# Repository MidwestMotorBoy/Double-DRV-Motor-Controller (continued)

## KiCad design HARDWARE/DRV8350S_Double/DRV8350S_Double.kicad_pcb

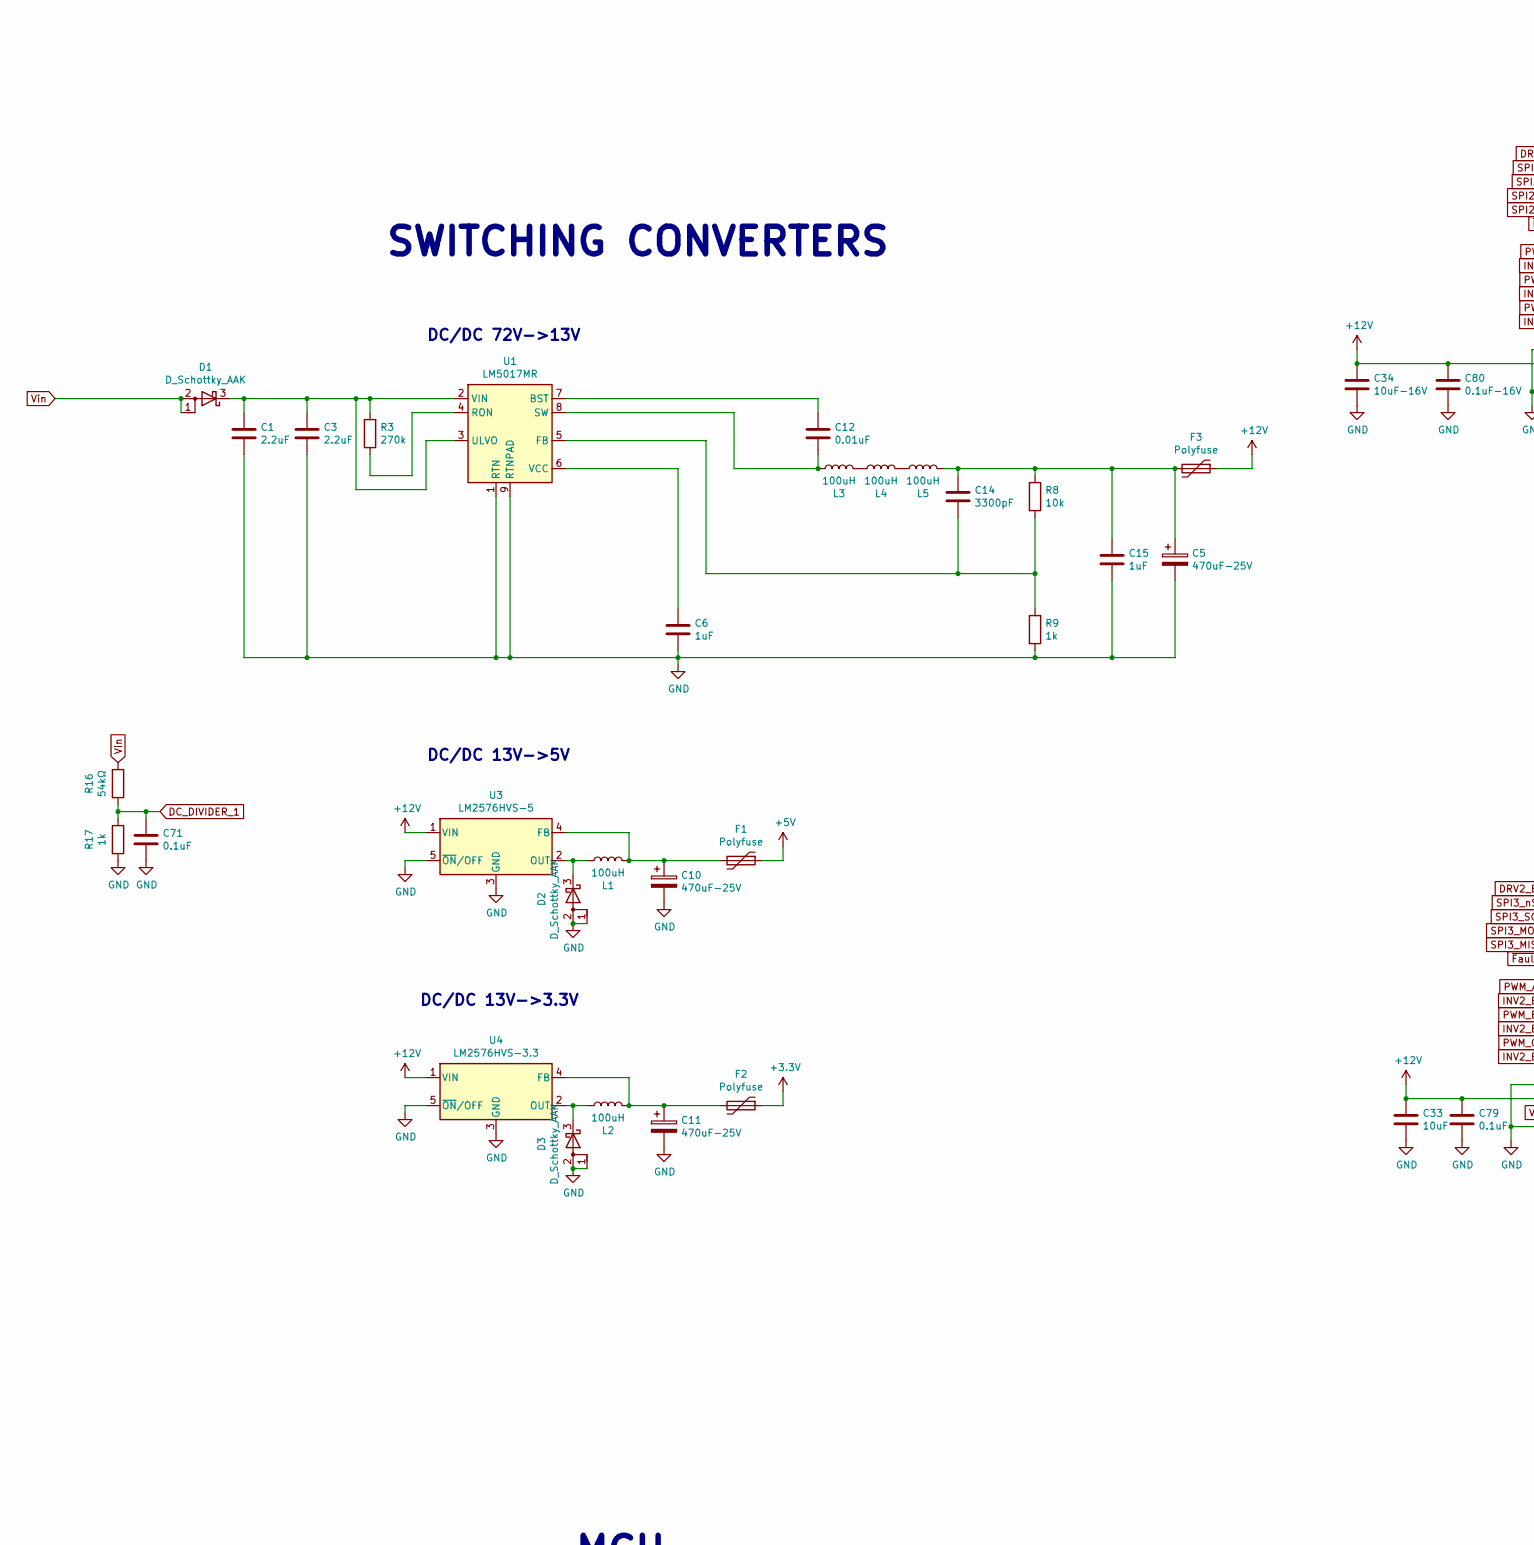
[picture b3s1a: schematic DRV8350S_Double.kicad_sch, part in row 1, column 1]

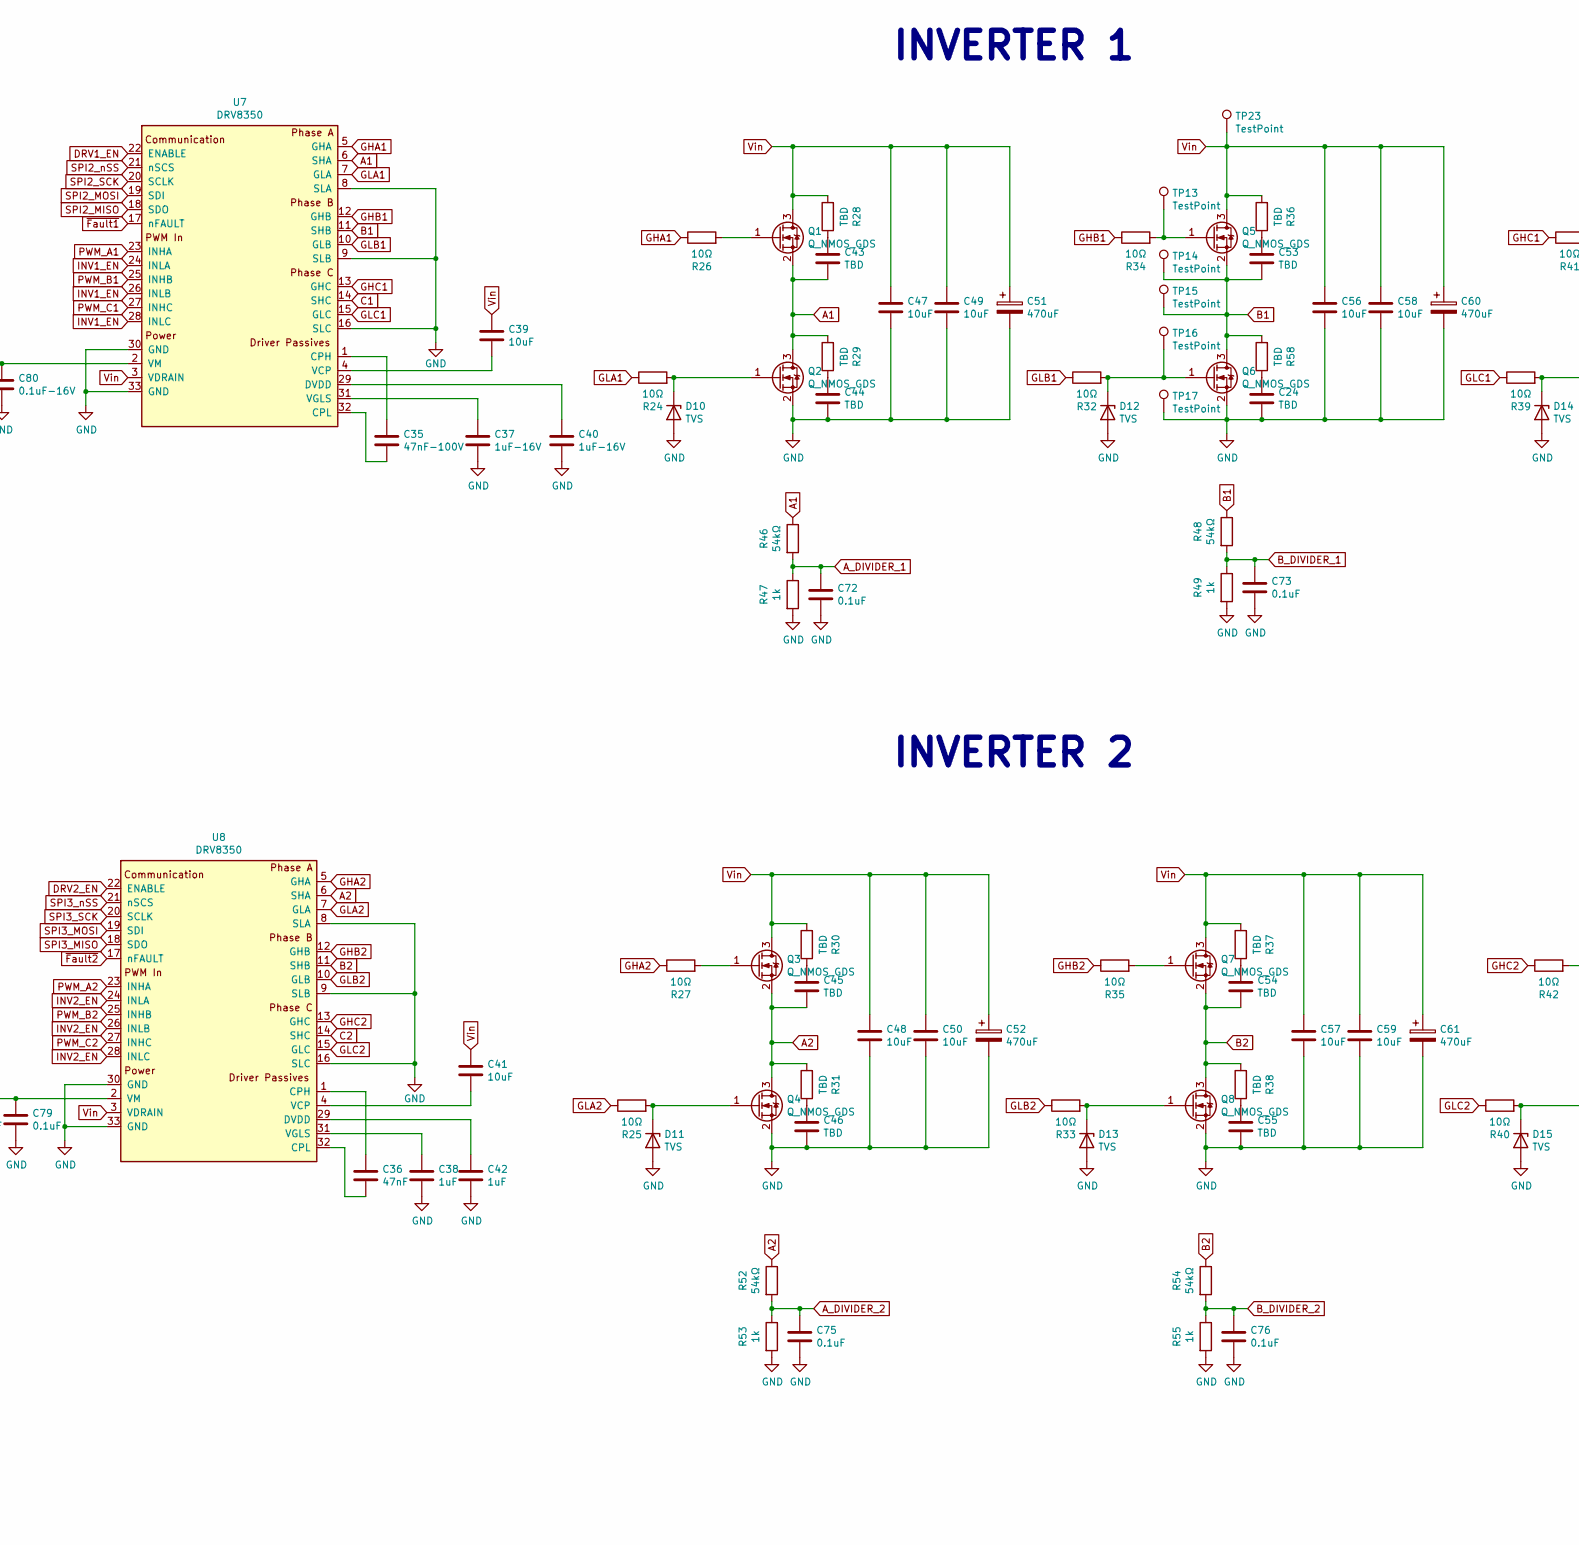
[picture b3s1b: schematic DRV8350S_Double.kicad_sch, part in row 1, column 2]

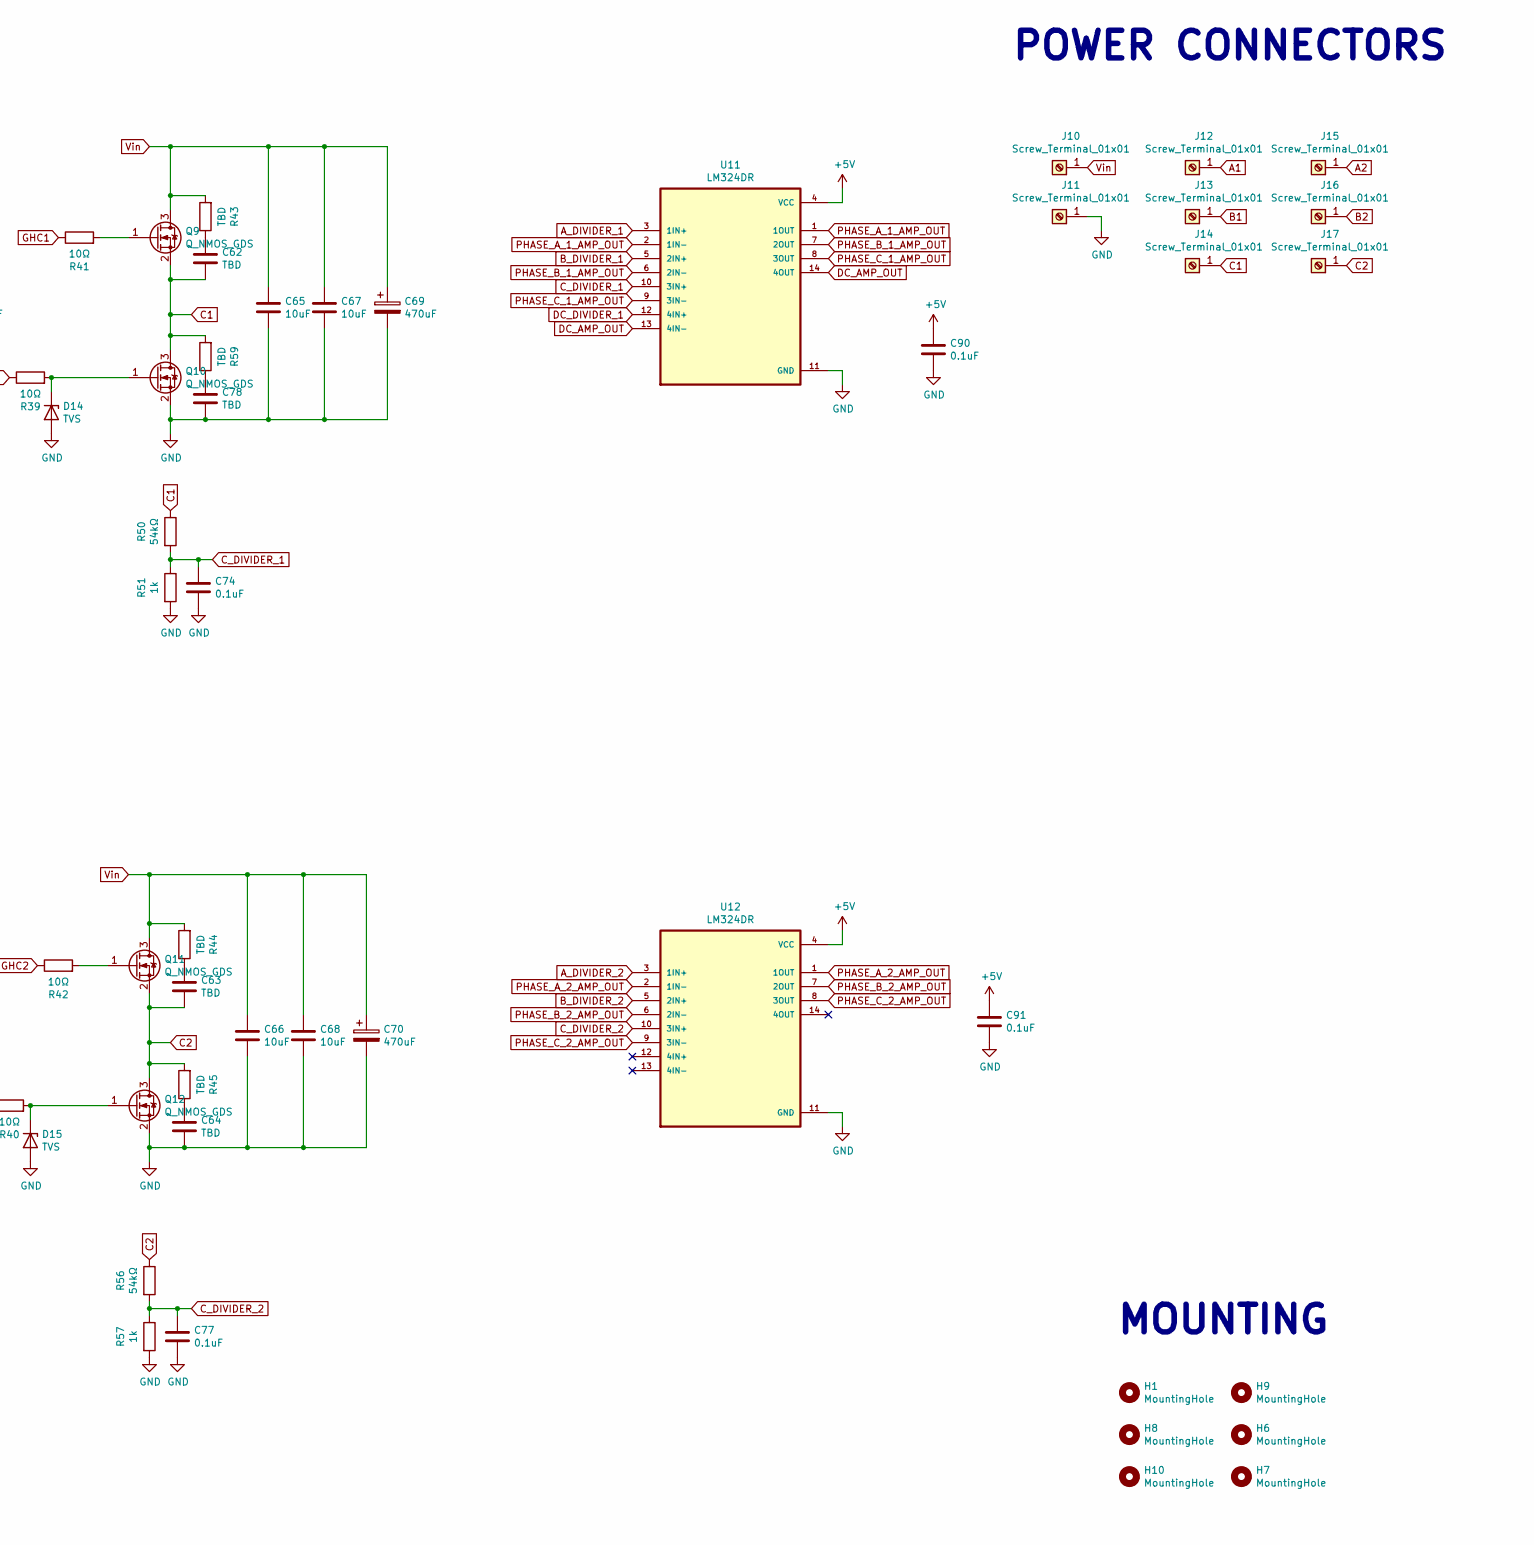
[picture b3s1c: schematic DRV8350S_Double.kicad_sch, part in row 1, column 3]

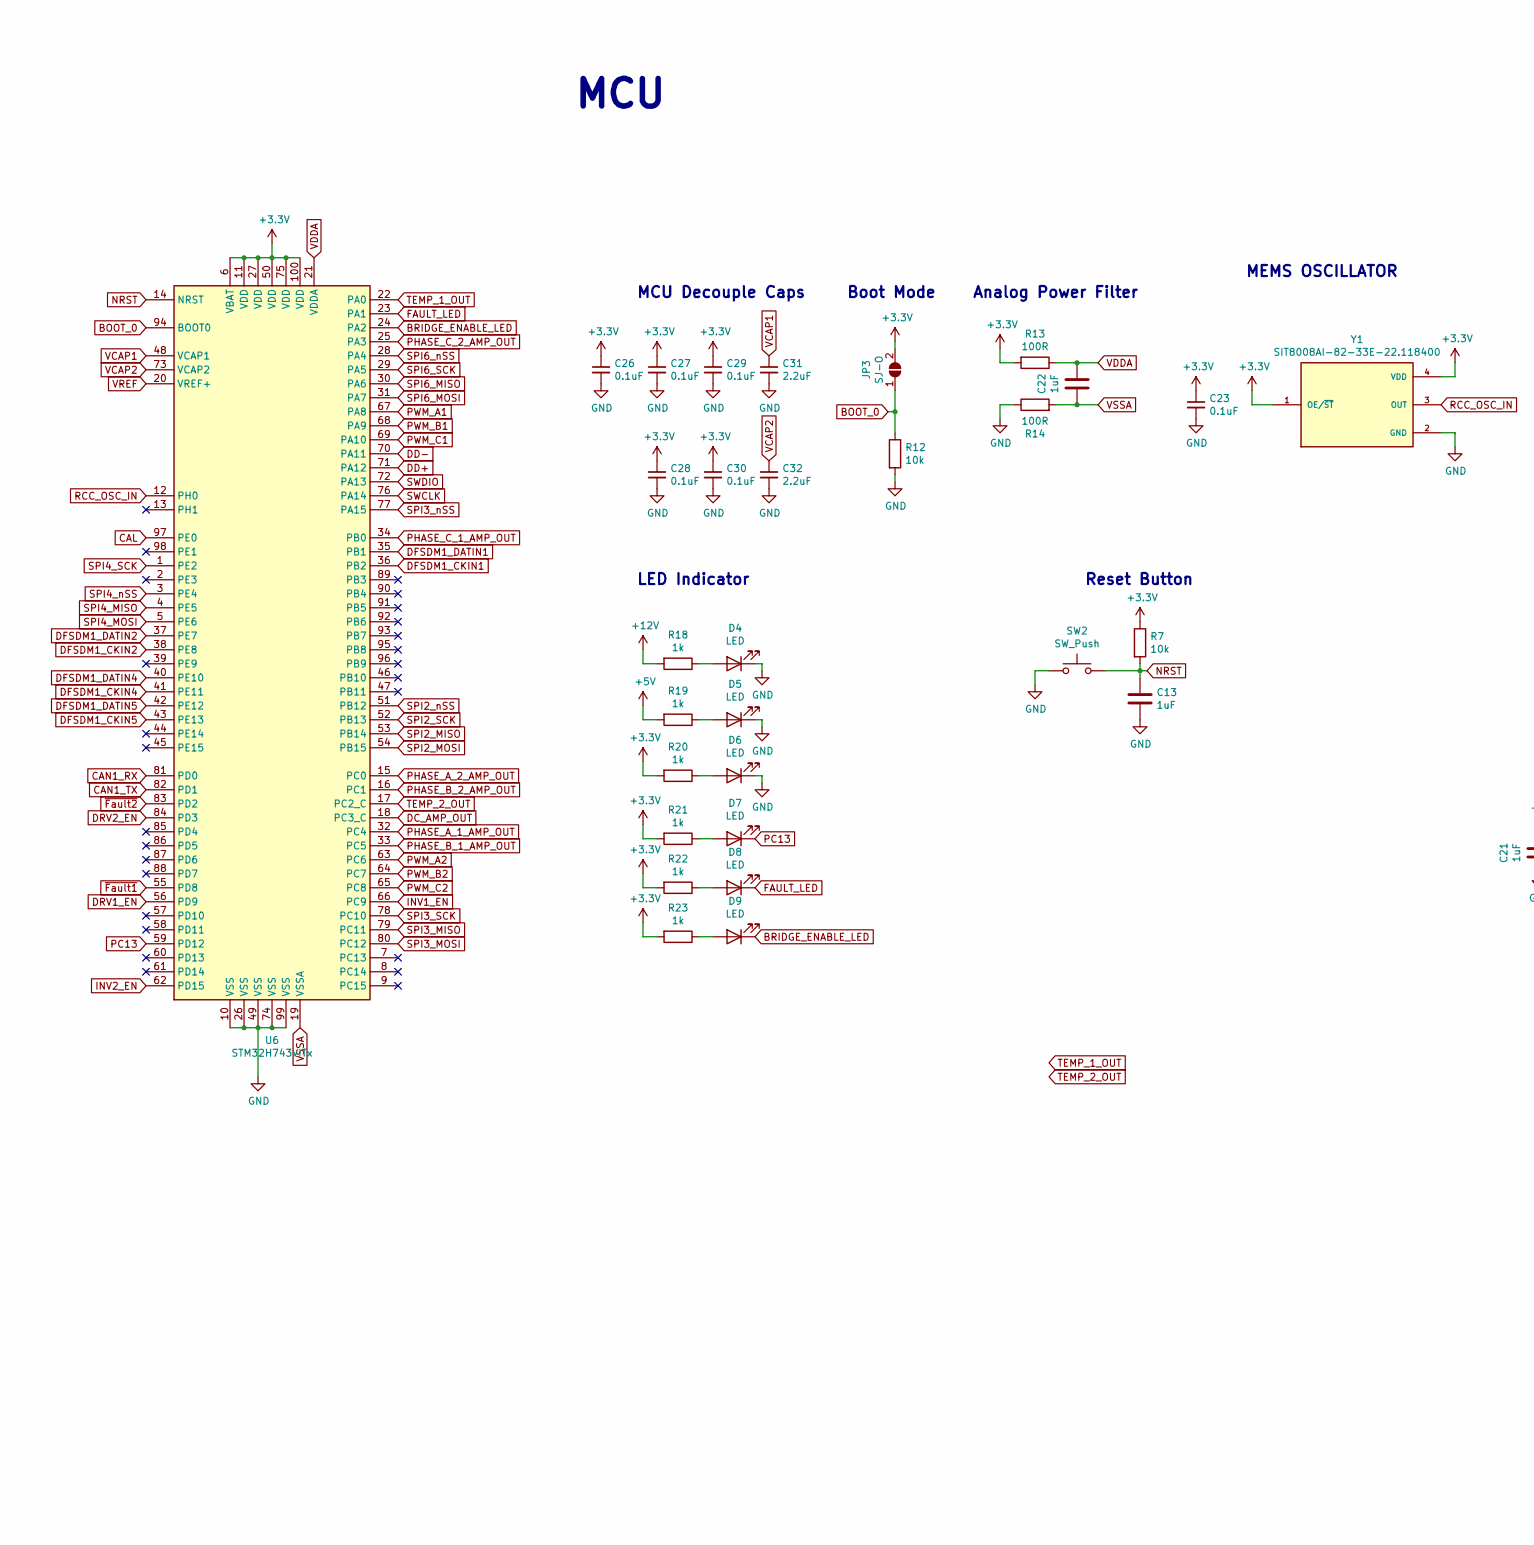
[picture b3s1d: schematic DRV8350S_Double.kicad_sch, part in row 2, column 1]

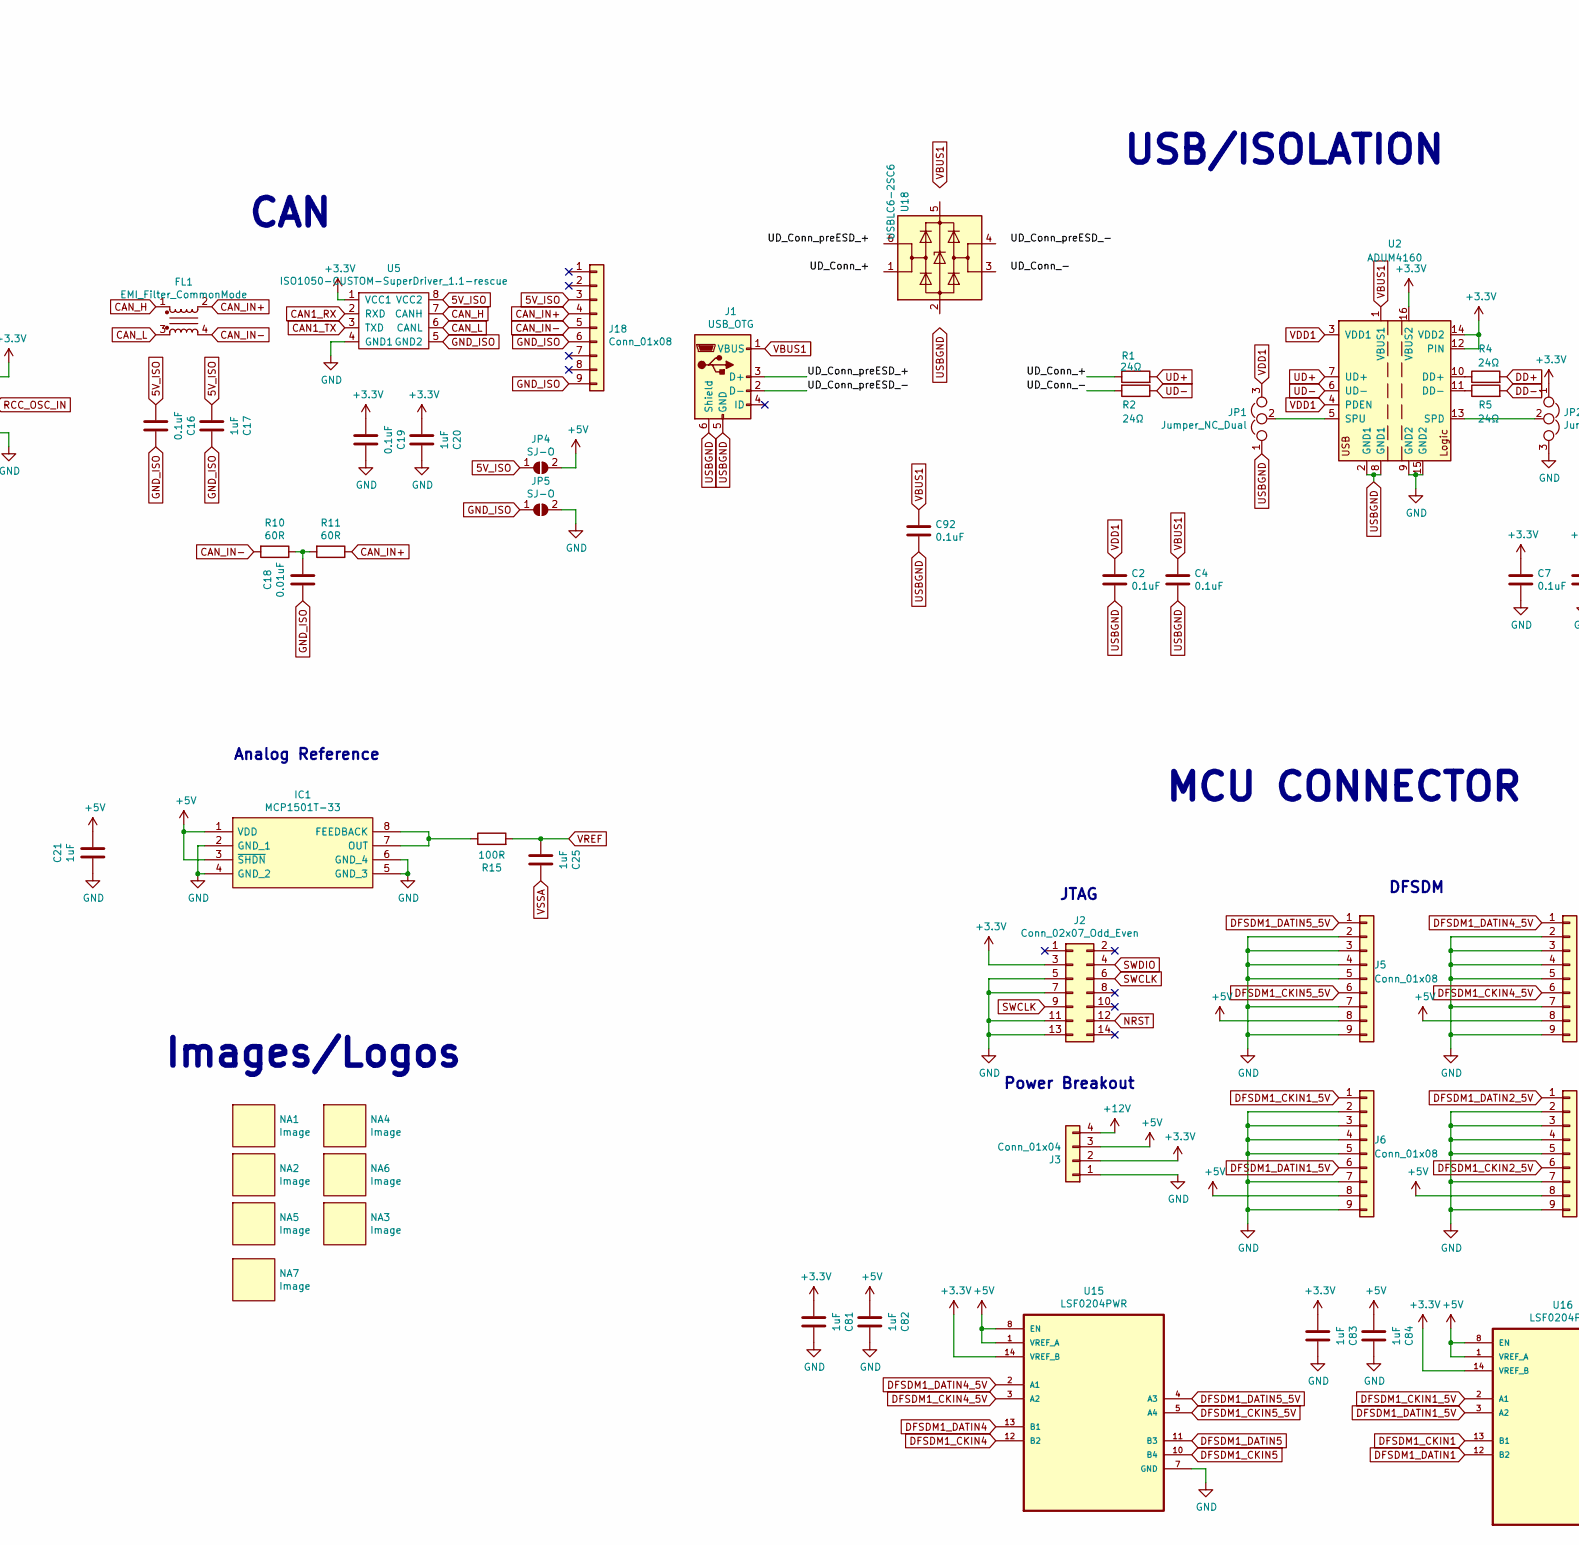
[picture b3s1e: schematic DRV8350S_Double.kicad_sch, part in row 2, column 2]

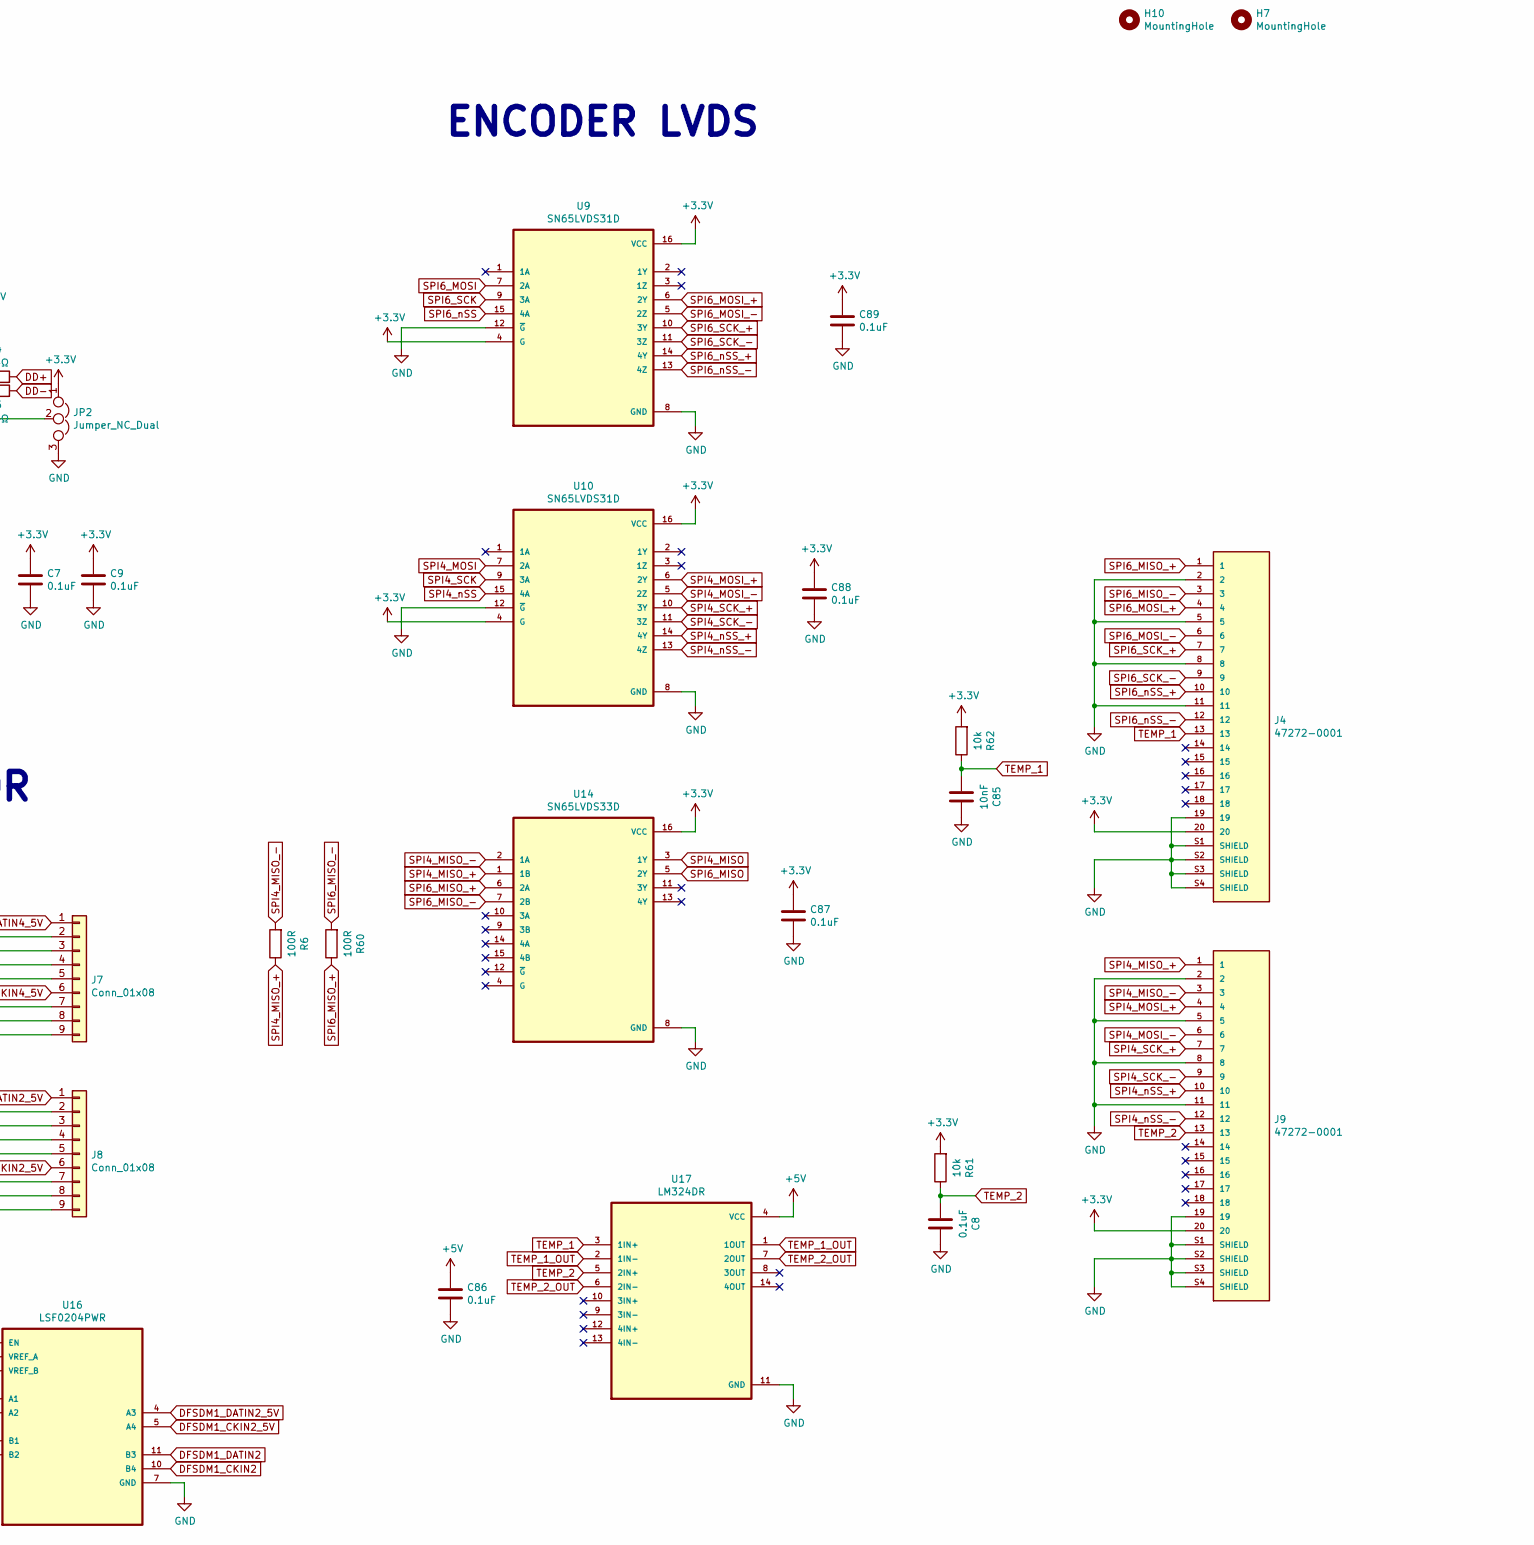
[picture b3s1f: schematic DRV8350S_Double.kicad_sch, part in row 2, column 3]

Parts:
C1, C3: 2.2uF; C_1206_3216Metric
C2, C4, C7, C8, C9, C16, C19, C23, C26, C27, C28, C29, C30, C71, C72, C73, C74, C75, C76, C77, C79, C86, C87, C88, C89, C90, C91, C92: 0.1uF; C_0603_1608Metric
C5, C10, C11: 470uF-25V; CP_Elec_10x10
C6, C13, C17, C20, C21, C22, C25, C38, C42, C81, C82, C83, C84: 1uF; C_0603_1608Metric
C12, C18: 0.01uF; C_0603_1608Metric
C14: 3300pF; C_0603_1608Metric
C15: 1uF; C_1206_3216Metric
C24, C43, C44, C45, C46, C53, C54, C55, C62, C63, C64, C78: TBD; C_0805_2012Metric
C31, C32: 2.2uF; C_0603_1608Metric
C33: 10uF; C_0603_1608Metric
C34: 10uF-16V; C_0603_1608Metric
C35: 47nF-100V; C_0805_2012Metric
C36: 47nF; C_0805_2012Metric
C37, C40: 1uF-16V; C_0603_1608Metric
C39, C41: 10uF; C_0805_2012Metric
C47, C48, C49, C50, C56, C57, C58, C59, C65, C66, C67, C68: 10uF; C_2220_5650Metric
C51, C52, C60, C61, C69, C70: 470uF; CAP_EEETP70471V
C80: 0.1uF-16V; C_0603_1608Metric
C85: 10nF; C_0603_1608Metric
D1, D2, D3: D_Schottky_AAK; TO-277A
D4, D5, D6, D7, D8, D9: LED; LED_0603_1608Metric
D10, D11, D12, D13, D14, D15: TVS; D_PowerDI-123
F1, F2, F3: Polyfuse; Fuse_1812_4532Metric
FL1: EMI_Filter_CommonMode; SRF2012A
H1, H6, H7, H8, H9, H10: MountingHole; MountingHole_3.2mm_M3
IC1: MCP1501T-33; SOIC127P600X175-8N; Mouser Part Number 579-MCP1501T-33E/SN
J1: USB_OTG; USB
J2: Conn_02x07_Odd_Even; PinHeader_2x07_P1.27mm_Vertical_SMD
J3: Conn_01x04; Molex_KK-254_AE-6410-04A_1x04_P2.54mm_Vertical
J4, J9: 47272-0001; MOLEX_47272-0001
J5, J6, J7, J8, J18: Conn_01x08; RCH-RC02015
J10, J11, J12, J13, J14, J15, J16, J17: Screw_Terminal_01x01; 7466005R‎_2ndapt
JP1, JP2: Jumper_NC_Dual; SolderJumper-3_P1.3mm_Open_RoundedPad1.0x1.5mm_NumberLabels
JP3, JP4, JP5: SJ-O; SolderJumper-2_P1.3mm_Open_TrianglePad1.0x1.5mm
L1, L2, L3, L4, L5: 100uH; L_Taiyo-Yuden_MD-5050
NA1: Image; blockI
NA2: Image; teamlogo
NA3: Image; qrcode_github
NA4: Image; voltage_warning
NA5: Image; Dont_get_brazen_with_me!
NA6: Image; biger
NA7: Image; qr_code_rick_roll
Q1, Q2, Q3, Q4, Q5, Q6, Q7, Q8, Q9, Q10, Q11, Q12: Q_NMOS_GDS; Infineon_PG-HSOF-8-1
R1, R2, R4, R5: 24Ω; R_0603_1608Metric
R3: 270k; R_0603_1608Metric
R6, R13, R14, R15, R60: 100R; R_0603_1608Metric
R7, R8, R12, R61, R62: 10k; R_0603_1608Metric
R9, R17, R18, R19, R20, R21, R22, R23, R47, R49, R51, R53, R55, R57: 1k; R_0603_1608Metric
R10, R11: 60R; R_0603_1608Metric
R16, R46, R48, R50, R52, R54, R56: 54kΩ; R_0603_1608Metric
R24, R25, R26, R27, R32, R33, R34, R35, R39, R40, R41, R42: 10Ω; R_0603_1608Metric
R28, R29, R30, R31, R36, R37, R38, R43, R44, R45, R58, R59: TBD; R_0805_2012Metric
SW2: SW_Push; SW_SPST_SKQG_WithStem
TP13, TP14, TP15, TP16, TP17, TP23: TestPoint; TestPoint_Keystone_5019_Minature
U1: LM5017MR; SOIC-8-1EP_3.9x4.9mm_P1.27mm_EP2.95x4.9mm_Mask2.71x3.4mm_Th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
U2: ADUM4160; SOIC-16W_7.5x10.3mm_P1.27mm
U3: LM2576HVS-5; TO-263-5_TabPin3
U4: LM2576HVS-3.3; TO-263-5_TabPin3
U5: ISO1050-CUSTOM-SuperDriver_1.1-rescue; SOP-8_6.62x9.15mm_P2.54mm
U6: STM32H743VITx; LQFP-100_14x14mm_P0.5mm
U7, U8: DRV8350; QFN-32-1EP_5x5mm_P0.5mm_EP3.45x3.45mm_ThermalVias
U9, U10: SN65LVDS31D; SOIC-16_3.9x9.9mm_P1.27mm
U11, U12, U17: LM324DR; SOIC-14_3.9x8.7mm_P1.27mm
U14: SN65LVDS33D; SOIC-16_3.9x9.9mm_P1.27mm
U15, U16: LSF0204PWR; TSSOP-14_4.4x5mm_P0.65mm
U18: USBLC6-2SC6; SOT-666
Y1: SIT8008AI-82-33E-22.118400; OSC_SIT8008AI-73-33E-33.333333G; PARTREV 1.11

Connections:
5V_ISO: C16.2, C17.1, J18.3, JP4.1 (A), U5.8 (VCC2)
+3V3: C7.1, C9.1, C19.2, C20.2, C23.1, C26.1, C27.1, C28.1, C29.1, C30.1, C81.2, C83.2, C87.1, C88.1, C89.1, F2.1, J2.3, J3.2, J4.20, J9.20, JP2.1, JP3.2 (B), R7.1, R13.2, R20.2, R21.2, R22.2, R23.2, R61.2, R62.2, U2.12 (PIN), U2.14 (VDD2), U2.16 (VBUS2), U5.1 (VCC1), U6.6 (VBAT), U6.11 (VDD), U6.27 (VDD), U6.50 (VDD), U6.75 (VDD), U6.100 (VDD), U9.4 (G), U9.16 (VCC), U10.4 (G), U10.16 (VCC), U14.16 (VCC), U15.14 (VREF_B), U16.14 (VREF_B), Y1.1 (OE/~ST), Y1.4 (VDD)
+5V: C21.1, C82.2, C84.2, C86.1, C90.1, C91.1, F1.1, IC1.1 (VDD), IC1.3 (~SHDN), J3.3, J5.8, J6.8, J7.8, J8.8, JP4.2 (B), R19.2, U11.4 (VCC), U12.4 (VCC), U15.1 (VREF_A), U15.8 (EN), U16.1 (VREF_A), U16.8 (EN), U17.4 (VCC)
+12V: C33.1, C34.1, C79.1, C80.1, F3.1, J3.4, R18.2, U3.1 (VIN), U4.1 (VIN), U7.2 (VM), U8.2 (VM)
/UD_Conn_+: R1.1, U18.1 (I/O1)
/UD_Conn_-: R2.2, U18.3 (I/O2)
/UD_Conn_preESD_+: J1.3 (D+), U18.6 (I/O1)
/UD_Conn_preESD_-: J1.2 (D-), U18.4 (I/O2)
A1: C43.2, J12.1, Q1.2 (S), Q2.3 (D), R29.2, R46.1, U7.6 (SHA)
A2: C45.2, J15.1, Q3.2 (S), Q4.3 (D), R31.2, R52.1, U8.6 (SHA)
A_DIVIDER_1: C72.1, R46.2, R47.1, U11.3 (1IN+)
A_DIVIDER_2: C75.1, R52.2, R53.1, U12.3 (1IN+)
B1: C53.2, J13.1, Q5.2 (S), Q6.3 (D), R48.1, R58.2, TP14.1, TP15.1, U7.11 (SHB)
B2: C54.2, J16.1, Q7.2 (S), Q8.3 (D), R38.2, R54.1, U8.11 (SHB)
BOOT_0: JP3.1 (A), R12.1, U6.94 (BOOT0)
BRIDGE_ENABLE_LED: D9.1 (K), U6.24 (PA2)
B_DIVIDER_1: C73.1, R48.2, R49.1, U11.5 (2IN+)
B_DIVIDER_2: C76.1, R54.2, R55.1, U12.5 (2IN+)
C1: C62.2, J14.1, Q9.2 (S), Q10.3 (D), R50.1, R59.2, U7.14 (SHC)
C2: C63.2, J17.1, Q11.2 (S), Q12.3 (D), R45.2, R56.1, U8.14 (SHC)
CAN1_RX: U5.2 (RXD), U6.81 (PD0)
CAN1_TX: U5.3 (TXD), U6.82 (PD1)
CAN_H: FL1.1, U5.7 (CANH)
CAN_IN+: FL1.2, J18.4, R11.1
CAN_IN-: FL1.4, J18.5, R10.2
CAN_L: FL1.3, U5.6 (CANL)
C_DIVIDER_1: C74.1, R50.2, R51.1, U11.10 (3IN+)
C_DIVIDER_2: C77.1, R56.2, R57.1, U12.10 (3IN+)
DC_AMP_OUT: U6.18 (PC3_C), U11.13 (4IN-), U11.14 (4OUT)
DC_DIVIDER_1: C71.1, R16.2, R17.1, U11.12 (4IN+)
DD+: R4.2, U6.71 (PA12)
DD-: R5.2, U6.70 (PA11)
DFSDM1_CKIN1: U6.36 (PB2), U16.13 (B1)
DFSDM1_CKIN1_5V: J6.1, U16.2 (A1)
DFSDM1_CKIN2: U6.38 (PE8), U16.10 (B4)
DFSDM1_CKIN2_5V: J8.6, U16.5 (A4)
DFSDM1_CKIN4: U6.41 (PE11), U15.12 (B2)
DFSDM1_CKIN4_5V: J7.6, U15.3 (A2)
DFSDM1_CKIN5: U6.43 (PE13), U15.10 (B4)
DFSDM1_CKIN5_5V: J5.6, U15.5 (A4)
DFSDM1_DATIN1: U6.35 (PB1), U16.12 (B2)
DFSDM1_DATIN1_5V: J6.6, U16.3 (A2)
DFSDM1_DATIN2: U6.37 (PE7), U16.11 (B3)
DFSDM1_DATIN2_5V: J8.1, U16.4 (A3)
DFSDM1_DATIN4: U6.40 (PE10), U15.13 (B1)
DFSDM1_DATIN4_5V: J7.1, U15.2 (A1)
DFSDM1_DATIN5: U6.42 (PE12), U15.11 (B3)
DFSDM1_DATIN5_5V: J5.1, U15.4 (A3)
DRV1_EN: U6.56 (PD9), U7.22 (ENABLE)
DRV2_EN: U6.84 (PD3), U8.22 (ENABLE)
FAULT_LED: D8.1 (K), U6.23 (PA1)
GHA1: R26.1, U7.5 (GHA)
GHA2: R27.1, U8.5 (GHA)
GHB1: R34.1, U7.12 (GHB)
GHB2: R35.1, U8.12 (GHB)
GHC1: R41.1, U7.13 (GHC)
GHC2: R42.1, U8.13 (GHC)
GLA1: R24.1, U7.7 (GLA)
GLA2: R25.1, U8.7 (GLA)
GLB1: R32.1, U7.10 (GLB)
GLB2: R33.1, U8.10 (GLB)
GLC1: R39.1, U7.15 (GLC)
GLC2: R40.1, U8.15 (GLC)
GND: C1.2, C3.2, C5.2, C6.2, C7.2, C8.1, C9.2, C10.2, C11.2, C13.2, C15.2, C19.1, C20.1, C21.2, C23.2, C24.2, C26.2, C27.2, C28.2, C29.2, C30.2, C31.2, C32.2, C33.2, C34.2, C37.2, C38.2, C40.2, C42.2, C44.2, C46.2, C47.2, C48.2, C49.2, C50.2, C51.2, C52.2, C55.2, C56.2, C57.2, C58.2, C59.2, C60.2, C61.2, C64.2, C65.2, C66.2, C67.2, C68.2, C69.2, C70.2, C71.2, C72.2, C73.2, C74.2, C75.2, C76.2, C77.2, C78.2, C79.2, C80.2, C81.1, C82.1, C83.1, C84.1, C85.1, C86.2, C87.2, C88.2, C89.2, C90.2, C91.2, D2.1 (A), D2.2 (A), D3.1 (A), D3.2 (A), D4.1 (K), D5.1 (K), D6.1 (K), D10.2 (A), D11.2 (A), D12.2 (A), D13.2 (A), D14.2 (A), D15.2 (A), IC1.2 (GND_1), IC1.4 (GND_2), IC1.5 (GND_3), IC1.6 (GND_4), J2.5, J2.7, J2.11, J2.13, J3.1, J4.2, J4.5, J4.8, J4.11, J4.19, J4.S1 (SHIELD), J4.S2 (SHIELD), J4.S3 (SHIELD), J4.S4 (SHIELD), J5.2, J5.3, J5.4, J5.5, J5.7, J5.9, J6.2, J6.3, J6.4, J6.5, J6.7, J6.9, J7.2, J7.3, J7.4, J7.5, J7.7, J7.9, J8.2, J8.3, J8.4, J8.5, J8.7, J8.9, J9.2, J9.5, J9.8, J9.11, J9.19, J9.S1 (SHIELD), J9.S2 (SHIELD), J9.S3 (SHIELD), J9.S4 (SHIELD), J11.1, JP2.3, JP5.2 (B), Q2.2 (S), Q4.2 (S), Q6.2 (S), Q8.2 (S), Q10.2 (S), Q12.2 (S), R9.2, R12.2, R14.1, R17.2, R47.2, R49.2, R51.2, R53.2, R55.2, R57.2, SW2.1, TP17.1, U1.1 (RTN), U1.9 (RTNPAD), U2.9 (GND2), U2.15 (GND2), U3.3 (GND), U3.5 (~ON/OFF), U4.3 (GND), U4.5 (~ON/OFF), U5.4 (GND1), U6.10 (VSS), U6.26 (VSS), U6.49 (VSS), U6.74 (VSS), U6.99 (VSS), U7.8 (SLA), U7.9 (SLB), U7.16 (SLC), U7.30 (GND), U7.33 (GND), U8.8 (SLA), U8.9 (SLB), U8.16 (SLC), U8.30 (GND), U8.33 (GND), U9.8 (GND), U9.12 (~G), U10.8 (GND), U10.12 (~G), U11.11 (GND), U12.11 (GND), U14.8 (GND), U15.7 (GND), U16.7 (GND), U17.11 (GND), Y1.2 (GND)
GND_ISO: C16.1, C17.2, C18.2, J18.6, J18.9, JP5.1 (A), U5.5 (GND2)
INV1_EN: U6.66 (PC9), U7.24 (INLA), U7.26 (INLB), U7.28 (INLC)
INV2_EN: U6.62 (PD15), U8.24 (INLA), U8.26 (INLB), U8.28 (INLC)
NRST: C13.1, J2.12, R7.2, SW2.2, U6.14 (NRST)
unnamed: C1.1, C3.1, D1.3 (K), R3.2, U1.2 (VIN), U1.3 (ULVO)
unnamed: C6.1, U1.6 (VCC)
unnamed: C10.1, F1.2, L1.2, U3.4 (FB)
unnamed: C11.1, F2.2, L2.2, U4.4 (FB)
unnamed: C12.1, U1.7 (BST)
unnamed: C12.2, L3.1, U1.8 (SW)
unnamed: C5.1, C14.1, C15.1, F3.2, L5.2, R8.1
unnamed: C14.2, R8.2, R9.1, U1.5 (FB)
unnamed: C18.1, R10.1, R11.2
unnamed: C24.1, R58.1
unnamed: C35.1, U7.1 (CPH)
unnamed: C35.2, U7.32 (CPL)
unnamed: C36.1, U8.1 (CPH)
unnamed: C36.2, U8.32 (CPL)
unnamed: C37.1, U7.31 (VGLS)
unnamed: C38.1, U8.31 (VGLS)
unnamed: C39.2, U7.4 (VCP)
unnamed: C40.1, U7.29 (DVDD)
unnamed: C41.2, U8.4 (VCP)
unnamed: C42.1, U8.29 (DVDD)
unnamed: C43.1, R28.1
unnamed: C44.1, R29.1
unnamed: C45.1, R30.1
unnamed: C46.1, R31.1
unnamed: C53.1, R36.1
unnamed: C54.1, R37.1
unnamed: C55.1, R38.1
unnamed: C62.1, R43.1
unnamed: C63.1, R44.1
unnamed: C64.1, R45.1
unnamed: C78.1, R59.1
unnamed: D2.3 (K), L1.1, U3.2 (OUT)
unnamed: D3.3 (K), L2.1, U4.2 (OUT)
unnamed: D4.2 (A), R18.1
unnamed: D5.2 (A), R19.1
unnamed: D6.2 (A), R20.1
unnamed: D7.2 (A), R21.1
unnamed: D8.2 (A), R22.1
unnamed: D9.2 (A), R23.1
unnamed: D10.1 (K), Q2.1 (G), R24.2
unnamed: D11.1 (K), Q4.1 (G), R25.2
unnamed: D12.1 (K), Q6.1 (G), R32.2, TP16.1
unnamed: D13.1 (K), Q8.1 (G), R33.2
unnamed: D14.1 (K), Q10.1 (G), R39.2
unnamed: D15.1 (K), Q12.1 (G), R40.2
unnamed: IC1.7 (OUT), IC1.8 (FEEDBACK), R15.1
unnamed: JP1.2, U2.5 (SPU)
unnamed: JP2.2, U2.13 (SPD)
unnamed: L3.2, L4.1
unnamed: L4.2, L5.1
unnamed: Q1.1 (G), R26.2
unnamed: Q3.1 (G), R27.2
unnamed: Q5.1 (G), R34.2, TP13.1
unnamed: Q7.1 (G), R35.2
unnamed: Q9.1 (G), R41.2
unnamed: Q11.1 (G), R42.2
unnamed: R3.1, U1.4 (RON)
unnamed: R4.1, U2.10 (DD+)
unnamed: R5.1, U2.11 (DD-)
PC13: D7.1 (K), U6.59 (PD12)
PHASE_A_1_AMP_OUT: U6.32 (PC4), U11.1 (1OUT), U11.2 (1IN-)
PHASE_A_2_AMP_OUT: U6.15 (PC0), U12.1 (1OUT), U12.2 (1IN-)
PHASE_B_1_AMP_OUT: U6.33 (PC5), U11.6 (2IN-), U11.7 (2OUT)
PHASE_B_2_AMP_OUT: U6.16 (PC1), U12.6 (2IN-), U12.7 (2OUT)
PHASE_C_1_AMP_OUT: U6.34 (PB0), U11.8 (3OUT), U11.9 (3IN-)
PHASE_C_2_AMP_OUT: U6.25 (PA3), U12.8 (3OUT), U12.9 (3IN-)
PWM_A1: U6.67 (PA8), U7.23 (INHA)
PWM_A2: U6.63 (PC6), U8.23 (INHA)
PWM_B1: U6.68 (PA9), U7.25 (INHB)
PWM_B2: U6.64 (PC7), U8.25 (INHB)
PWM_C1: U6.69 (PA10), U7.27 (INHC)
PWM_C2: U6.65 (PC8), U8.27 (INHC)
RCC_OSC_IN: U6.12 (PH0), Y1.3 (OUT)
SPI2_MISO: U6.53 (PB14), U7.18 (SDO)
SPI2_MOSI: U6.54 (PB15), U7.19 (SDI)
SPI2_SCK: U6.52 (PB13), U7.20 (SCLK)
SPI2_nSS: U6.51 (PB12), U7.21 (nSCS)
SPI3_MISO: U6.79 (PC11), U8.18 (SDO)
SPI3_MOSI: U6.80 (PC12), U8.19 (SDI)
SPI3_SCK: U6.78 (PC10), U8.20 (SCLK)
SPI3_nSS: U6.77 (PA15), U8.21 (nSCS)
SPI4_MISO: U6.4 (PE5), U14.3 (1Y)
SPI4_MISO_+: J9.1, R6.1, U14.1 (1B)
SPI4_MISO_-: J9.3, R6.2, U14.2 (1A)
SPI4_MOSI: U6.5 (PE6), U10.7 (2A)
SPI4_MOSI_+: J9.4, U10.6 (2Y)
SPI4_MOSI_-: J9.6, U10.5 (2Z)
SPI4_SCK: U6.1 (PE2), U10.9 (3A)
SPI4_SCK_+: J9.7, U10.10 (3Y)
SPI4_SCK_-: J9.9, U10.11 (3Z)
SPI4_nSS: U6.3 (PE4), U10.15 (4A)
SPI4_nSS_+: J9.10, U10.14 (4Y)
SPI4_nSS_-: J9.12, U10.13 (4Z)
SPI6_MISO: U6.30 (PA6), U14.5 (2Y)
SPI6_MISO_+: J4.1, R60.1, U14.6 (2A)
SPI6_MISO_-: J4.3, R60.2, U14.7 (2B)
SPI6_MOSI: U6.31 (PA7), U9.7 (2A)
SPI6_MOSI_+: J4.4, U9.6 (2Y)
SPI6_MOSI_-: J4.6, U9.5 (2Z)
SPI6_SCK: U6.29 (PA5), U9.9 (3A)
SPI6_SCK_+: J4.7, U9.10 (3Y)
SPI6_SCK_-: J4.9, U9.11 (3Z)
SPI6_nSS: U6.28 (PA4), U9.15 (4A)
SPI6_nSS_+: J4.10, U9.14 (4Y)
SPI6_nSS_-: J4.12, U9.13 (4Z)
SWCLK: J2.6, J2.9, U6.76 (PA14)
SWDIO: J2.4, U6.72 (PA13)
TEMP_1: C85.2, J4.13, R62.1, U17.3 (1IN+)
TEMP_1_OUT: U6.22 (PA0), U17.1 (1OUT), U17.2 (1IN-)
TEMP_2: C8.2, J9.13, R61.1, U17.5 (2IN+)
TEMP_2_OUT: U6.17 (PC2_C), U17.6 (2IN-), U17.7 (2OUT)
UD+: R1.2, U2.7 (UD+)
UD-: R2.1, U2.6 (UD-)
USBGND: C2.2, C4.2, C92.2, J1.5 (GND), J1.6 (Shield), JP1.1, U2.2 (GND1), U2.8 (GND1), U18.2 (GND)
VBUS1: C4.1, C92.1, J1.1 (VBUS), U2.1 (VBUS1), U18.5 (VBUS)
VCAP1: C31.1, U6.48 (VCAP1)
VCAP2: C32.1, U6.73 (VCAP2)
VDD1: C2.1, JP1.3, U2.3 (VDD1), U2.4 (PDEN)
VDDA: C22.1, R13.1, U6.21 (VDDA)
VREF: C25.2, R15.2, U6.20 (VREF+)
VSSA: C22.2, C25.1, R14.2, U6.19 (VSSA)
Vin: C39.1, C41.1, C47.1, C48.1, C49.1, C50.1, C51.1, C52.1, C56.1, C57.1, C58.1, C59.1, C60.1, C61.1, C65.1, C66.1, C67.1, C68.1, C69.1, C70.1, D1.1 (A), D1.2 (A), J10.1, Q1.3 (D), Q3.3 (D), Q5.3 (D), Q7.3 (D), Q9.3 (D), Q11.3 (D), R16.1, R28.2, R30.2, R36.2, R37.2, R43.2, R44.2, TP23.1, U7.3 (VDRAIN), U8.3 (VDRAIN)
~Fault1: U6.55 (PD8), U7.17 (nFAULT)
~Fault2: U6.83 (PD2), U8.17 (nFAULT)

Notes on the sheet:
CAN
MCU
SWITCHING CONVERTERS
INVERTER 1
Images/Logos
USB/ISOLATION
DC/DC 13V->3.3V
ENCODER LVDS
DFSDM
Power Breakout
Boot Mode
DC/DC 13V->5V
LED Indicator
MCU CONNECTOR
POWER CONNECTORS
Analog Power Filter
DC/DC 72V->13V
Analog Reference
MOUNTING
INVERTER 2
JTAG
MCU Decouple Caps
MEMS OSCILLATOR
Reset Button
